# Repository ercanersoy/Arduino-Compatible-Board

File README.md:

# Arduino Compatible Board

Arduino Compatible Board for professional use

The circuit designed by Arduino.
Some changes applied by Ercan Ersoy.

This work is licensed under CC-BY-SA 4.0 License.

## 3D Model

## Note

Arduino is a trademark of Arduino Company.

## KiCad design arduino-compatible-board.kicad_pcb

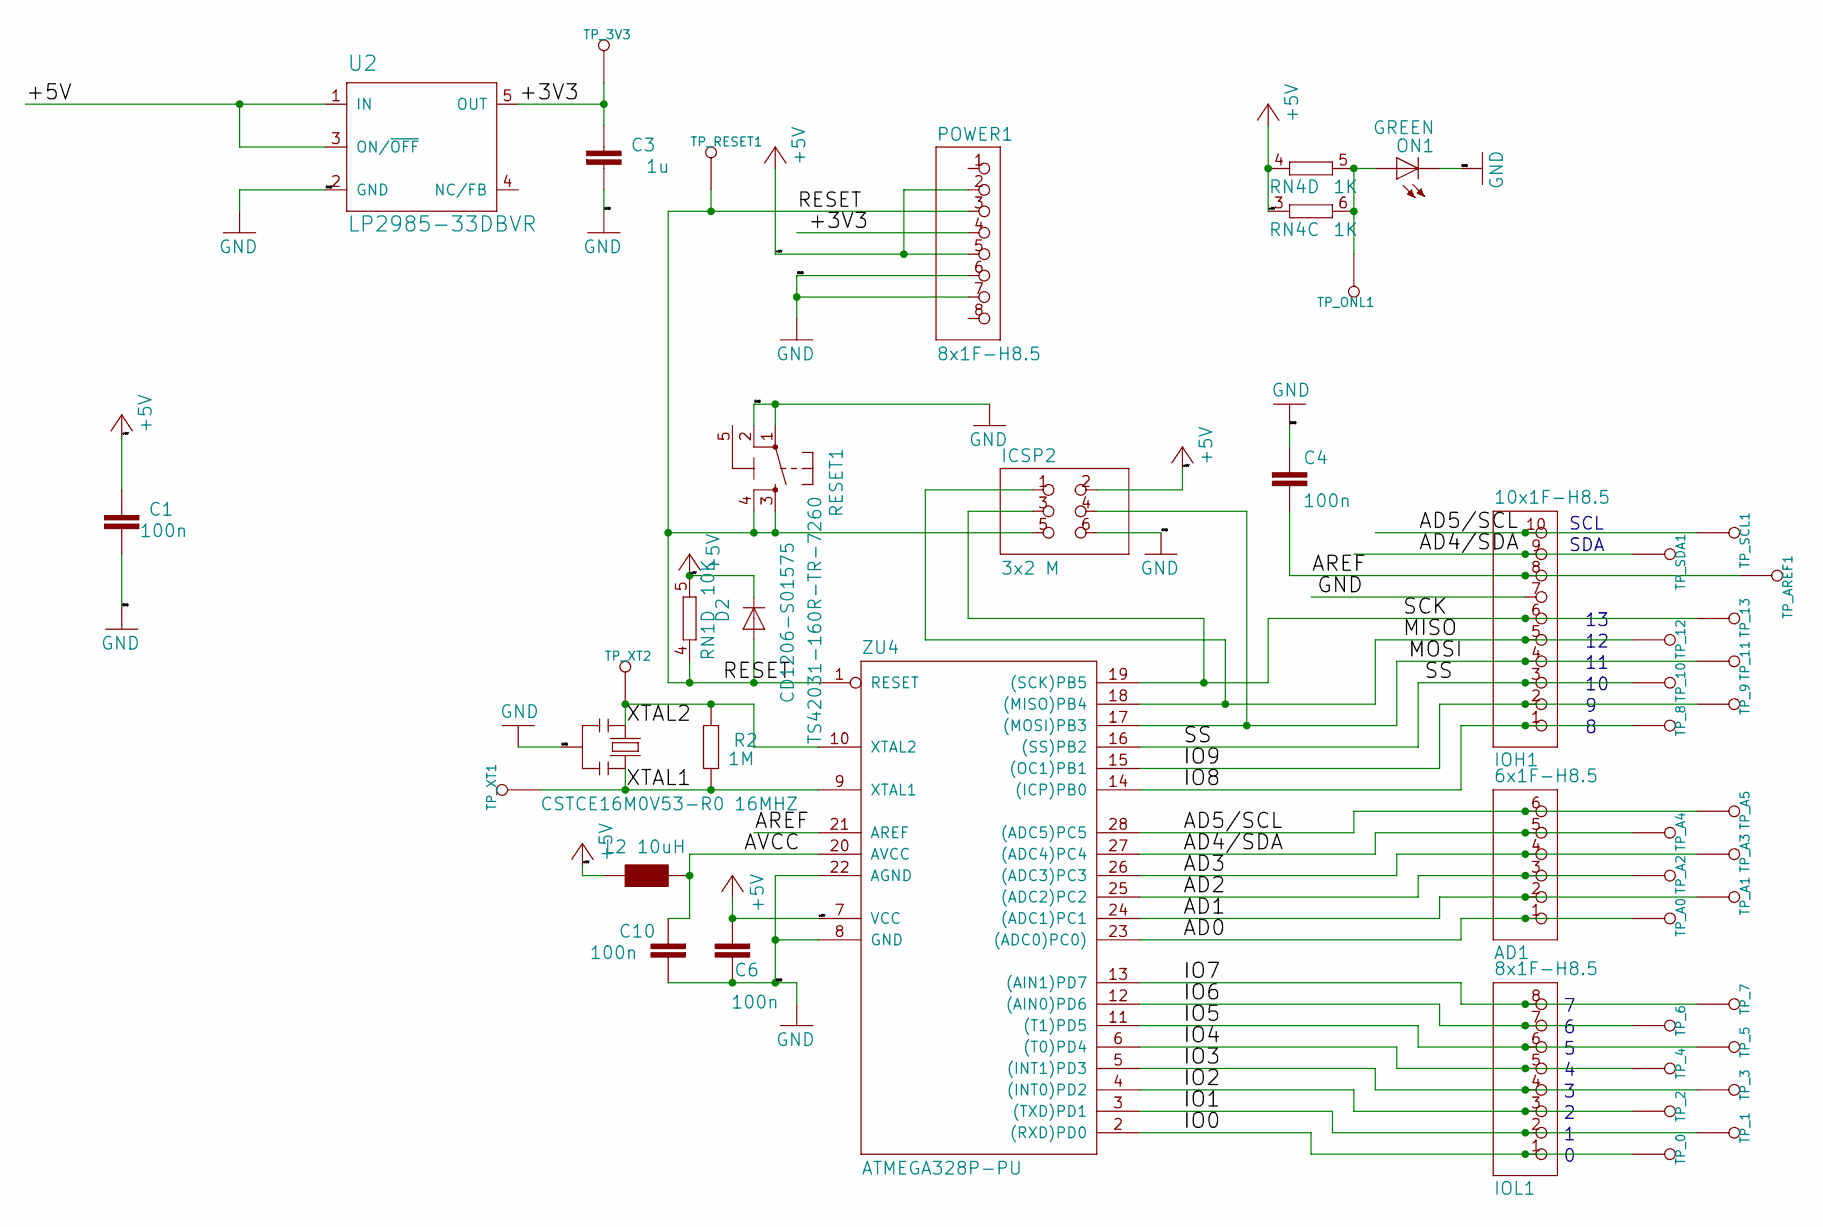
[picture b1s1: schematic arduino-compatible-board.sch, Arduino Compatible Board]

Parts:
AD1: 6x1F-H8.5; 1X06
C1, C4, C6, C10: 100n; C0603-ROUND
C3: 1u; C0603-ROUND
D2: CD1206-S01575; MINIMELF
ICSP2: 3x2 M; 2X03
IOH1: 10x1F-H8.5; 1X10
IOL1: 8x1F-H8.5; 1X08
L2: 10uH; 0805
ON1: GREEN; CHIP-LED0805
POWER1: 8x1F-H8.5; 1X08
R2: 1M; R0603-ROUND
RESET1: TS42031-160R-TR-7260; TS42
RN1: 10K; CAY16
RN4: 1K; CAY16
TP_0, TP_1, TP_2, TP_3, TP_3V3, TP_4, TP_5, TP_6, TP_7, TP_8, TP_9, TP_10, TP_11, TP_12, TP_13: TP_SP; TP-SP
TP_A0, TP_A1, TP_A2, TP_A3, TP_A4, TP_A5: TP_SP; TP-SP
TP_AREF1: TP_SP; TP-SP
TP_ONL1: TP_SP; TP-SP
TP_RESET1: TP_SP; TP-SP
TP_SCL1: TP_SP; TP-SP
TP_SDA1: TP_SP; TP-SP
TP_XT1, TP_XT2: TP_SP; TP-SP
U2: LP2985-33DBVR; SOT23-DBV
Y2: CSTCE16M0V53-R0 16MHZ; RESONATOR
ZU4: ATMEGA328P-PU; DIL28-3

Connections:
+5V: C1.2, C6.2, D2.C, ICSP2.2, L2.1, POWER1.2, POWER1.5, RN1.5 (2), RN4.3 (1), RN4.4 (1), U2.1 (IN), U2.3 (ON/~OFF), ZU4.7 (VCC)
/+3V3: C3.2, POWER1.4, TP_3V3.X, U2.5 (OUT)
/AD0: AD1.1, TP_A0.X, ZU4.23 ((ADC0)PC0))
/AD1: AD1.2, TP_A1.X, ZU4.24 ((ADC1)PC1)
/AD2: AD1.3, TP_A2.X, ZU4.25 ((ADC2)PC2)
/AD3: AD1.4, TP_A3.X, ZU4.26 ((ADC3)PC3)
/AD4/SDA: AD1.5, IOH1.9, TP_A4.X, TP_SDA1.X, ZU4.27 ((ADC4)PC4)
/AD5/SCL: AD1.6, IOH1.10, TP_A5.X, TP_SCL1.X, ZU4.28 ((ADC5)PC5)
/AREF: C4.2, IOH1.8, TP_AREF1.X, ZU4.21 (AREF)
/AVCC: C10.2, L2.2, ZU4.20 (AVCC)
/IO0: IOL1.1, TP_0.X, ZU4.2 ((RXD)PD0)
/IO1: IOL1.2, TP_1.X, ZU4.3 ((TXD)PD1)
/IO2: IOL1.3, TP_2.X, ZU4.4 ((INT0)PD2)
/IO3: IOL1.4, TP_3.X, ZU4.5 ((INT1)PD3)
/IO4: IOL1.5, TP_4.X, ZU4.6 ((T0)PD4)
/IO5: IOL1.6, TP_5.X, ZU4.11 ((T1)PD5)
/IO6: IOL1.7, TP_6.X, ZU4.12 ((AIN0)PD6)
/IO7: IOL1.8, TP_7.X, ZU4.13 ((AIN1)PD7)
/IO8: IOH1.1, TP_8.X, ZU4.14 ((ICP)PB0)
/IO9: IOH1.2, TP_9.X, ZU4.15 ((OC1)PB1)
/MISO: ICSP2.1, IOH1.5, TP_12.X, ZU4.18 ((MISO)PB4)
/MOSI: ICSP2.4, IOH1.4, TP_11.X, ZU4.17 ((MOSI)PB3)
/RESET: D2.A, ICSP2.5, POWER1.3, RESET1.3, RESET1.4, RN1.4 (1), TP_RESET1.X, ZU4.1 (RESET)
/SCK: ICSP2.3, IOH1.6, TP_13.X, ZU4.19 ((SCK)PB5)
/SS: IOH1.3, TP_10.X, ZU4.16 ((SS)PB2)
/XTAL1: R2.1, TP_XT1.X, Y2.3, ZU4.9 (XTAL1)
/XTAL2: R2.2, TP_XT2.X, Y2.1, ZU4.10 (XTAL2)
GND: C1.1, C3.1, C4.1, C6.1, C10.1, ICSP2.6, IOH1.7, ON1.C, POWER1.6, POWER1.7, RESET1.1, RESET1.2, U2.2 (GND), Y2.2, ZU4.8 (GND), ZU4.22 (AGND)
unnamed: ON1.A, RN4.5 (2), RN4.6 (2), TP_ONL1.X

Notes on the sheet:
SDA
SCL

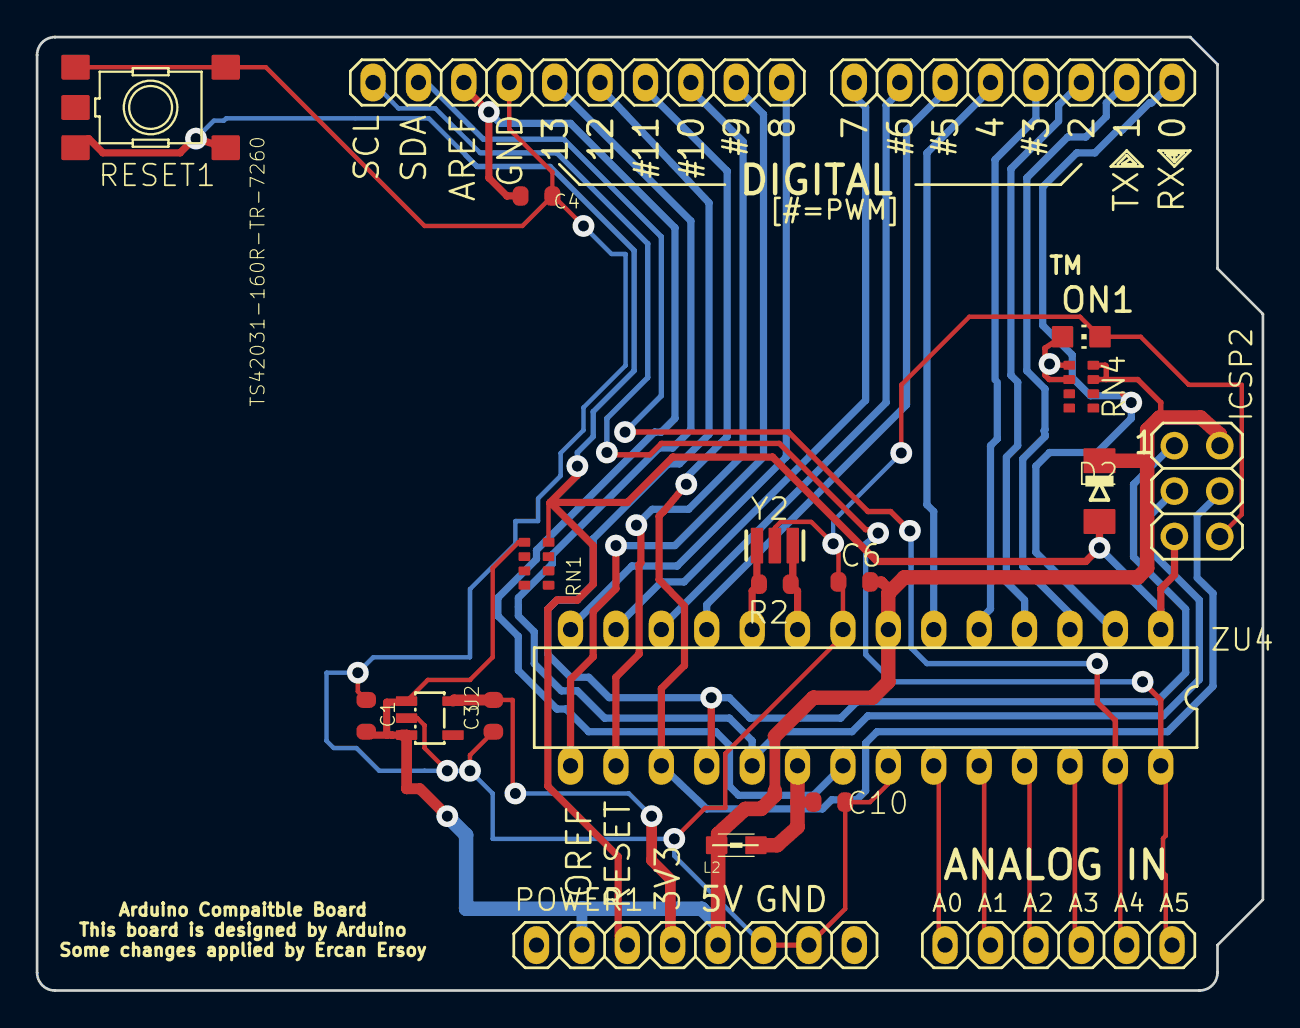
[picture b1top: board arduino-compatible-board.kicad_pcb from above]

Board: 2 copper layers, 68.6 x 53.3 mm, 48 parts (0 on the bottom side), 29 nets.

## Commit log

2021-06-19 Add LICENSE, README.md and hardware files
2021-06-19 Update README.md file
    Add trademark information to README.md file
2021-06-19 Add 3d model backplane
2021-06-19 Update PCB file and 3D model image files

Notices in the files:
arduino-compatible-board.sch:
This scehmatic licensed under CC-BY-SA 4.0
